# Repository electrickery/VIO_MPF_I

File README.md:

This repository contains the firmware versions for the Bardhele Electronic
VIDEO-MPF-I card. 

More info on my home page: https://www.electrickery.nl/comp/mpf1/index.html

VIO.zip are the hex dumps of the original ROMs that came with the card.

These are the most interesting entry addresses as of version 2.2:

* 0a000h:   clear screen, reset cursor 

* 0a004h:	init 6845, clear screen, return from call
 
* 0a007h:	init 6845, clear screen, jump to 0000h

* 0a00ah:	(JCRTCO) print character in C, interpret control codes

* 0a00dh:	(JCRTOU) print character in C, print codes 00h-31h too

* 0a010h:	(JTEXCO) print 00h terminated string (start in IY)

* 0a013h:	(JTEXCLN) print 00h terminated string (start in IY) with line end (CR/LF)

* 0a016h:	writes character set to screen, jump to 0000h

* 0a019h:   init 6845, clear screen, print banner, rst 0

* 0a01Fh:   hex/ascii memory dump of 8 * 16 bytes, rst 0

The hardware is configured for 8 bit wide, 11 bit high characters, 
limiting the screen to 40 x 20 characters (PAL timing). A proper video 
standard is useful as it allows usage of small, cheap TFT screens.

The assembly code is not very well understood, and used to contain multiple 
usages of un-occupied memory (0ff04h - 0ffcch range). It works, as long as
all unused memory returns 0FFh (EPROM installed). This dead code is now
succesfully removed now (entry points still work). It may have been part of a 
debugging tool.

The new code is initially assembled for and tested via the MicroProfessor 
U7 socket at 02000h. The VIO-MPF-I 1.2 PCB ROM 0A000h socket also works. 

Screenshot of the first page of the Monitor ROM:

Schema of the original Bardhele VIDEO-MPF-I:

The 8x9 FONT ROM works ok with the 40x25 mode:

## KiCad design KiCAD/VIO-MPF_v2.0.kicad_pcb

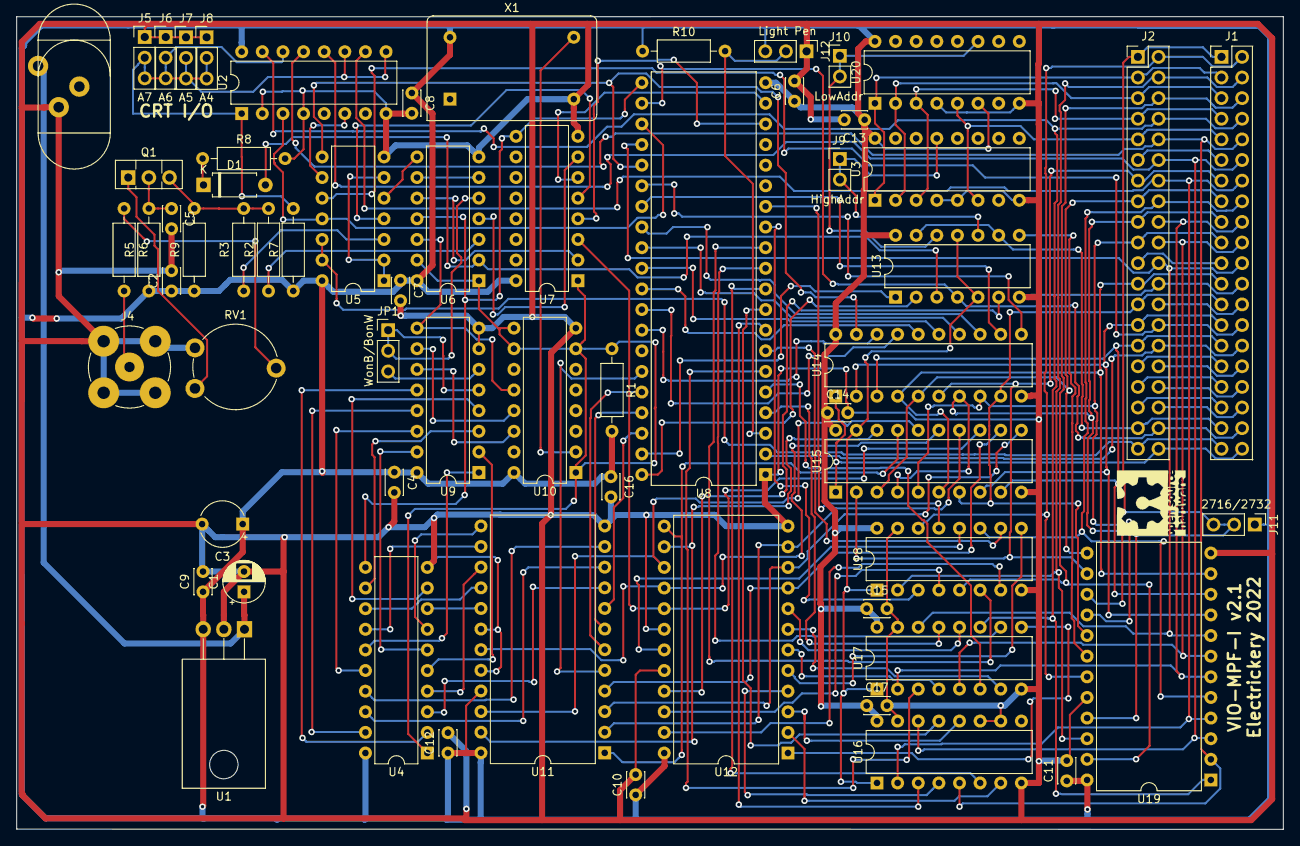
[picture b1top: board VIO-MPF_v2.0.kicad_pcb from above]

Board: 2 copper layers, 156.0 x 100.1 mm, 63 parts (0 on the bottom side), 137 nets.

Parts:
C1: 2.2uF; CP_Radial_D5.0mm_P2.50mm
C2, C4, C6, C7, C8, C9, C10, C11, C12, C13, C14, C15, C16, C17: 0.1uF; C_Disc_D3.0mm_W2.0mm_P2.50mm
C3: 100uF; CP_Radial_Tantal_D5.5mm_P5.00mm
C5: 22pF; C_Disc_D3.0mm_W2.0mm_P2.50mm
D1: 1N4148W; D_A-405_P7.62mm_Horizontal
J1, J2: MPF-BUS; PinHeader_2x20_P2.54mm_Vertical_CW
J3: Barrel_Jack; Barrel_Jack_vertical_alt
J4: Conn_Coaxial; BNC_TEConnectivity_1478204_Vertical
J5: A7; PinHeader_1x03_P2.54mm_Vertical
J6: A6; PinHeader_1x03_P2.54mm_Vertical
J7: A5; PinHeader_1x03_P2.54mm_Vertical
J8: A4; PinHeader_1x03_P2.54mm_Vertical
J9: HighAddr; PinHeader_1x02_P2.54mm_Vertical
J10: LowAddr; PinHeader_1x02_P2.54mm_Vertical
J11: 2716/2732; PinHeader_1x03_P2.54mm_Vertical
J12: Light Pen; PinHeader_1x03_P2.54mm_Vertical
JP1: WonB/BonW; PinHeader_1x03_P2.54mm_Vertical
Q1: BF459; TO-126-3_Vertical
R1, R7, R10: 3k3; R_Axial_DIN0207_L6.3mm_D2.5mm_P10.16mm_Horizontal
R2: 330; R_Axial_DIN0207_L6.3mm_D2.5mm_P10.16mm_Horizontal
R3: 390; R_Axial_DIN0207_L6.3mm_D2.5mm_P10.16mm_Horizontal
R5: 10; R_Axial_DIN0207_L6.3mm_D2.5mm_P10.16mm_Horizontal
R6: 27; R_Axial_DIN0207_L6.3mm_D2.5mm_P10.16mm_Horizontal
R8: 1k; R_Axial_DIN0207_L6.3mm_D2.5mm_P10.16mm_Horizontal
R9: 120; R_Axial_DIN0207_L6.3mm_D2.5mm_P10.16mm_Horizontal
RV1: 220; Potentiometer_Piher_PT-10-V10_Vertical
U1: uA7805; TO-220-3_Horizontal_TabDown
U2: 74LS85; DIP-16_W7.62mm
U3, U20: 74LS138; DIP-16_W7.62mm
U4: 74LS273; DIP-20_W7.62mm
U5: 74LS00; DIP-14_W7.62mm
U6: 74LS86; DIP-14_W7.62mm
U7: 74LS174; DIP-16_W7.62mm
U8: MC6845; DIP-40_W15.24mm
U9: 74LS151; DIP-16_W7.62mm
U10: 74LS161; DIP-16_W7.62mm
U11: 2716_alt; DIP-24_W15.24mm
U12: 6116_alt; DIP-24_W15.24mm
U13: 74LS32; DIP-14_W7.62mm
U14, U15: 74LS245; DIP-20_W7.62mm
U16, U17, U18: 74LS157; DIP-16_W7.62mm
U19: 2732_alt; DIP-24_W15.24mm
X1: ACO-8.0MHz; Oscillator_DIP-14

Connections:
/4xxx: J10.1, J10.2, U13.12, U20.11
/AD0: J1.30, J2.30, U8.24, U17.14, U19.8
/AD1: J1.31, J2.31, U17.5, U19.7
/AD2: J1.32, J2.32, U17.2, U19.6
/AD3: J1.33, J2.33, U18.11, U19.5
/AD4: J1.34, J2.34, U2.10, U16.2, U19.4
/AD5: J1.35, J2.35, U2.12, U16.14, U19.3
/AD6: J1.36, J2.36, U2.13, U16.5, U19.2
/AD7: J1.37, J2.37, U2.15, U17.11, U19.1
/AD8: J1.38, J2.38, U18.5, U19.23
/AD9: J1.39, J2.39, U18.2, U19.22
/AD10: J1.40, J2.40, U18.14, U19.19
/AD11: J1.1, J2.1, J11.2, J11.3, U19.21
/AD12: J1.2, J2.2, U3.1, U20.1
/AD13: J1.3, J2.3, U3.2, U20.2
/AD14: J1.4, J2.4, U3.3, U20.3
/AD15: J1.5, J2.5, U3.6, U20.5
/Axxxh: J9.1, J9.2, U3.13, U13.10
/BUSAK*: J1.23, J2.23
/BUSRQ*: J1.25, J2.25
/CU: U7.6, U8.19
/CURSOR1: U6.4, U7.7
/D0: J1.14, J2.14, U14.2, U15.8, U19.9
/D1: J1.15, J2.15, U14.3, U15.9, U19.10
/D01: U11.4, U12.9, U15.12
/D2: J1.12, J2.12, U14.4, U15.6, U19.11
/D3: J1.8, J2.8, U14.5, U15.3, U19.13
/D4: J1.7, J2.7, U14.6, U15.2, U19.14
/D5: J1.9, J2.9, U14.7, U15.4, U19.15
/D6: J1.10, J2.10, U14.8, U15.5, U19.16
/D7: J1.13, J2.13, U14.9, U15.7, U19.17
/D11: U11.3, U12.10, U15.11
/D21: U11.2, U12.11, U15.14
/D31: U11.1, U12.13, U15.17
/D41: U11.23, U12.14, U15.18
/D51: U11.22, U12.15, U15.16
/D61: U11.19, U12.16, U15.15
/D71: U7.3, U12.17, U15.13
/DB0: U8.33, U14.18
/DB1: U8.32, U14.17
/DB2: U8.31, U14.16
/DB3: U8.30, U14.15
/DB4: U8.29, U14.14
/DB5: U8.28, U14.13
/DB6: U8.27, U14.12
/DB7: U8.26, U14.11
/DEN: U7.4, U8.18
/DEN1: U5.4, U7.5
/EXT: J1.11, J2.11
/HLT*: J1.18, J2.18
/HSBL*: U13.5, U13.11, U15.19, U16.1, U17.1, U18.1
/HSYNC: U8.39, U13.1
/I*: U6.10, U7.2
/INT*: J1.16, J2.16
/IORQ1: U2.3, U5.11, U8.23
/IORQ*: J1.20, J2.20, U5.12, U5.13
/MI*: J1.27, J2.27, U5.10
/MR-W*: U12.21, U13.6
/MREQ*: J1.19, J2.19, U13.9, U13.13
/NMI*: J1.17, J2.17
/P0: U4.2, U9.12
/P1: U4.19, U9.13
/P2: U4.16, U9.14
/P3: U4.6, U9.15
/P4: U4.15, U9.1
/P5: U4.5, U9.2
/P6: U4.12, U9.3
/P7: U4.9, U9.4
/PHI0: J1.6, J2.6
/PU: R1.1, U4.1, U6.1, U6.13, U7.1, U10.1, U10.7, U10.9, U10.10
/RA0: U8.38, U11.8
/RA1: U8.37, U11.7
/RA2: U8.36, U11.6
/RA3: U8.35, U11.5
/RD*: J1.21, J2.21, U14.1, U15.1
/RFSH*: J1.28, J2.28
/RS*: J1.26, J2.26, U8.2
/SER*: U13.8, U19.18
/V0: U12.8, U17.12
/V1: U12.7, U17.7
/V2: U12.6, U17.4
/V3: U12.5, U18.9
/V4: U12.4, U16.4
/V5: U12.3, U16.12
/V6: U12.2, U16.7
/V7: U12.1, U17.9
/V8: U12.23, U18.7
/V9: U12.22, U18.4
/V10: U12.19, U18.12
/VA0: U8.4, U17.13
/VA1: U8.5, U17.6
/VA2: U8.6, U17.3
/VA3: U8.7, U18.10
/VA4: U8.8, U16.3
/VA5: U8.9, U16.13
/VA6: U8.10, U16.6
/VA7: U8.11, U17.10
/VA8: U8.12, U18.6
/VA9: U8.13, U18.3
/VA10: U8.14, U18.13
/VD0: U4.3, U11.9
/VD1: U4.18, U11.10
/VD2: U4.17, U11.11
/VD3: U4.7, U11.13
/VD4: U4.14, U11.14
/VD5: U4.4, U11.15
/VD6: U4.13, U11.16
/VD7: U4.8, U11.17
/VIDEO: JP1.1, JP1.2, U6.5, U9.5
/VSYNC: U8.40, U13.2
/WAIT*: J1.24, J2.24
/WR*: J1.22, J2.22, U8.22, U13.4
/ZTKT*: U4.11, U6.11, U7.9, U8.21
GND: C1.2, C2.2, C3.2, C4.2, C5.2, C6.2, C7.2, C8.2, C9.2, C10.2, C11.2, C12.2, C13.2, C14.2, C15.2, C16.2, C17.2, J1.29, J2.29, J3.2, J4.2, J5.1, J6.1, J7.1, J8.1, J12.1, R8.2, RV1.3, U1.2, U2.2, U2.4, U2.8, U3.4, U3.5, U3.8, U4.10, U5.7, U6.7, U7.8, U8.1, U9.7, U9.8, U10.8, U11.12, U11.18, U11.20, U12.12, U12.18, U12.20, U13.7, U14.10, U15.10, U16.8, U16.10, U16.11, U16.15, U17.8, U17.15, U18.8, U18.15, U19.12, U19.20, U20.4, U20.8, X1.7
unnamed: C1.1, J3.1, U1.1
unnamed: C5.1, Q1.2, R5.2
unnamed: D1.1, R8.1
unnamed: D1.2, U6.2, U13.3
unnamed: J4.1, R6.2
unnamed: J5.2, J5.3, J6.2, J6.3, J7.2, J7.3, J8.2, J8.3, R7.2, U2.1, U2.9, U2.11, U2.14
unnamed: J12.2, R10.2, U8.3
unnamed: JP1.3, U9.6
unnamed: Q1.1, RV1.1
unnamed: Q1.3, R2.2, R3.2, R9.2
unnamed: R2.1, U6.3
unnamed: R3.1, U5.3
unnamed: R6.1, RV1.2
unnamed: U2.6, U5.9
unnamed: U5.1, U5.2, U5.6
unnamed: U5.5, U6.8
unnamed: U6.6, U6.9
unnamed: U10.2, X1.8
unnamed: U6.12, U9.9, U10.12
unnamed: U9.10, U10.13
unnamed: U9.11, U10.14
unnamed: U5.8, U8.25, U14.19
VCC: C2.1, C3.1, C4.1, C6.1, C7.1, C8.1, C9.1, C10.1, C11.1, C12.1, C13.1, C14.1, C15.1, C16.1, C17.1, J11.1, J12.3, R1.2, R5.1, R7.1, R9.1, R10.1, U1.3, U2.16, U3.16, U4.20, U5.14, U6.14, U7.16, U8.20, U9.16, U10.16, U11.21, U11.24, U12.24, U13.14, U14.20, U15.20, U16.16, U17.16, U18.16, U19.24, U20.6, U20.16, X1.14

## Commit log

2022-02-06 First version after disassembly, with minor annotations.
2022-02-06 Version with only the character mangling removed.
2022-02-06 Timing now closer to true PAL, more annotations, banner added.
2022-02-06 More documentation.
2022-02-06 More formatting.
2022-02-08 Added 8 * 16 bytes HEX/ASCII memory dump.
2022-02-08 Doc updates.
2022-02-08 More documentation updates.
2022-02-08 Replaced schema with the correct version 1.2.
2022-02-08 Cleanup dead code part1.
2022-02-08 Cleanup dead code part2.
2022-02-08 More code and documentation cleanup.
2022-02-08 Added the CLS entry point to doc.
2022-02-08 Added dead-code removal success to doc.
2022-02-14 Cleanup of potential continious loops, and fixed the control character jump table.
2022-02-14 Minor fixes & additions.
2022-02-17 Schema (1.x and 2.0) and KiCAD board files (2.0).
2022-02-17 Control character fix.
2022-02-18 Added images of the default 8x11 pixel font ROM.
2022-02-18 Added KiCAD files for the 2.1 version.
2022-02-19 ASCII presentations of the original 8x11 and the edited 8x9 font ROM.
2022-02-25 Moved 8x11 font files, added 8x9 files.
2022-02-25 Cleaned font files.
2022-03-27 Preliminary manual. Far from complete.
2022-04-01 Even more documentation.
2022-04-03 More manual and image of 8x9 font / 40x25 mode.
2022-04-04 Switched to 40x25 display geometry, v2.3.
2022-04-05 Split off applications in separate file. Added CRT Register dump.
2022-04-06 Added some more annotation to disassembled code.
2022-04-06 Minor manual updates.
2025-09-27 Added note on default setting by PCB trace J11 (firmware EPROM).
